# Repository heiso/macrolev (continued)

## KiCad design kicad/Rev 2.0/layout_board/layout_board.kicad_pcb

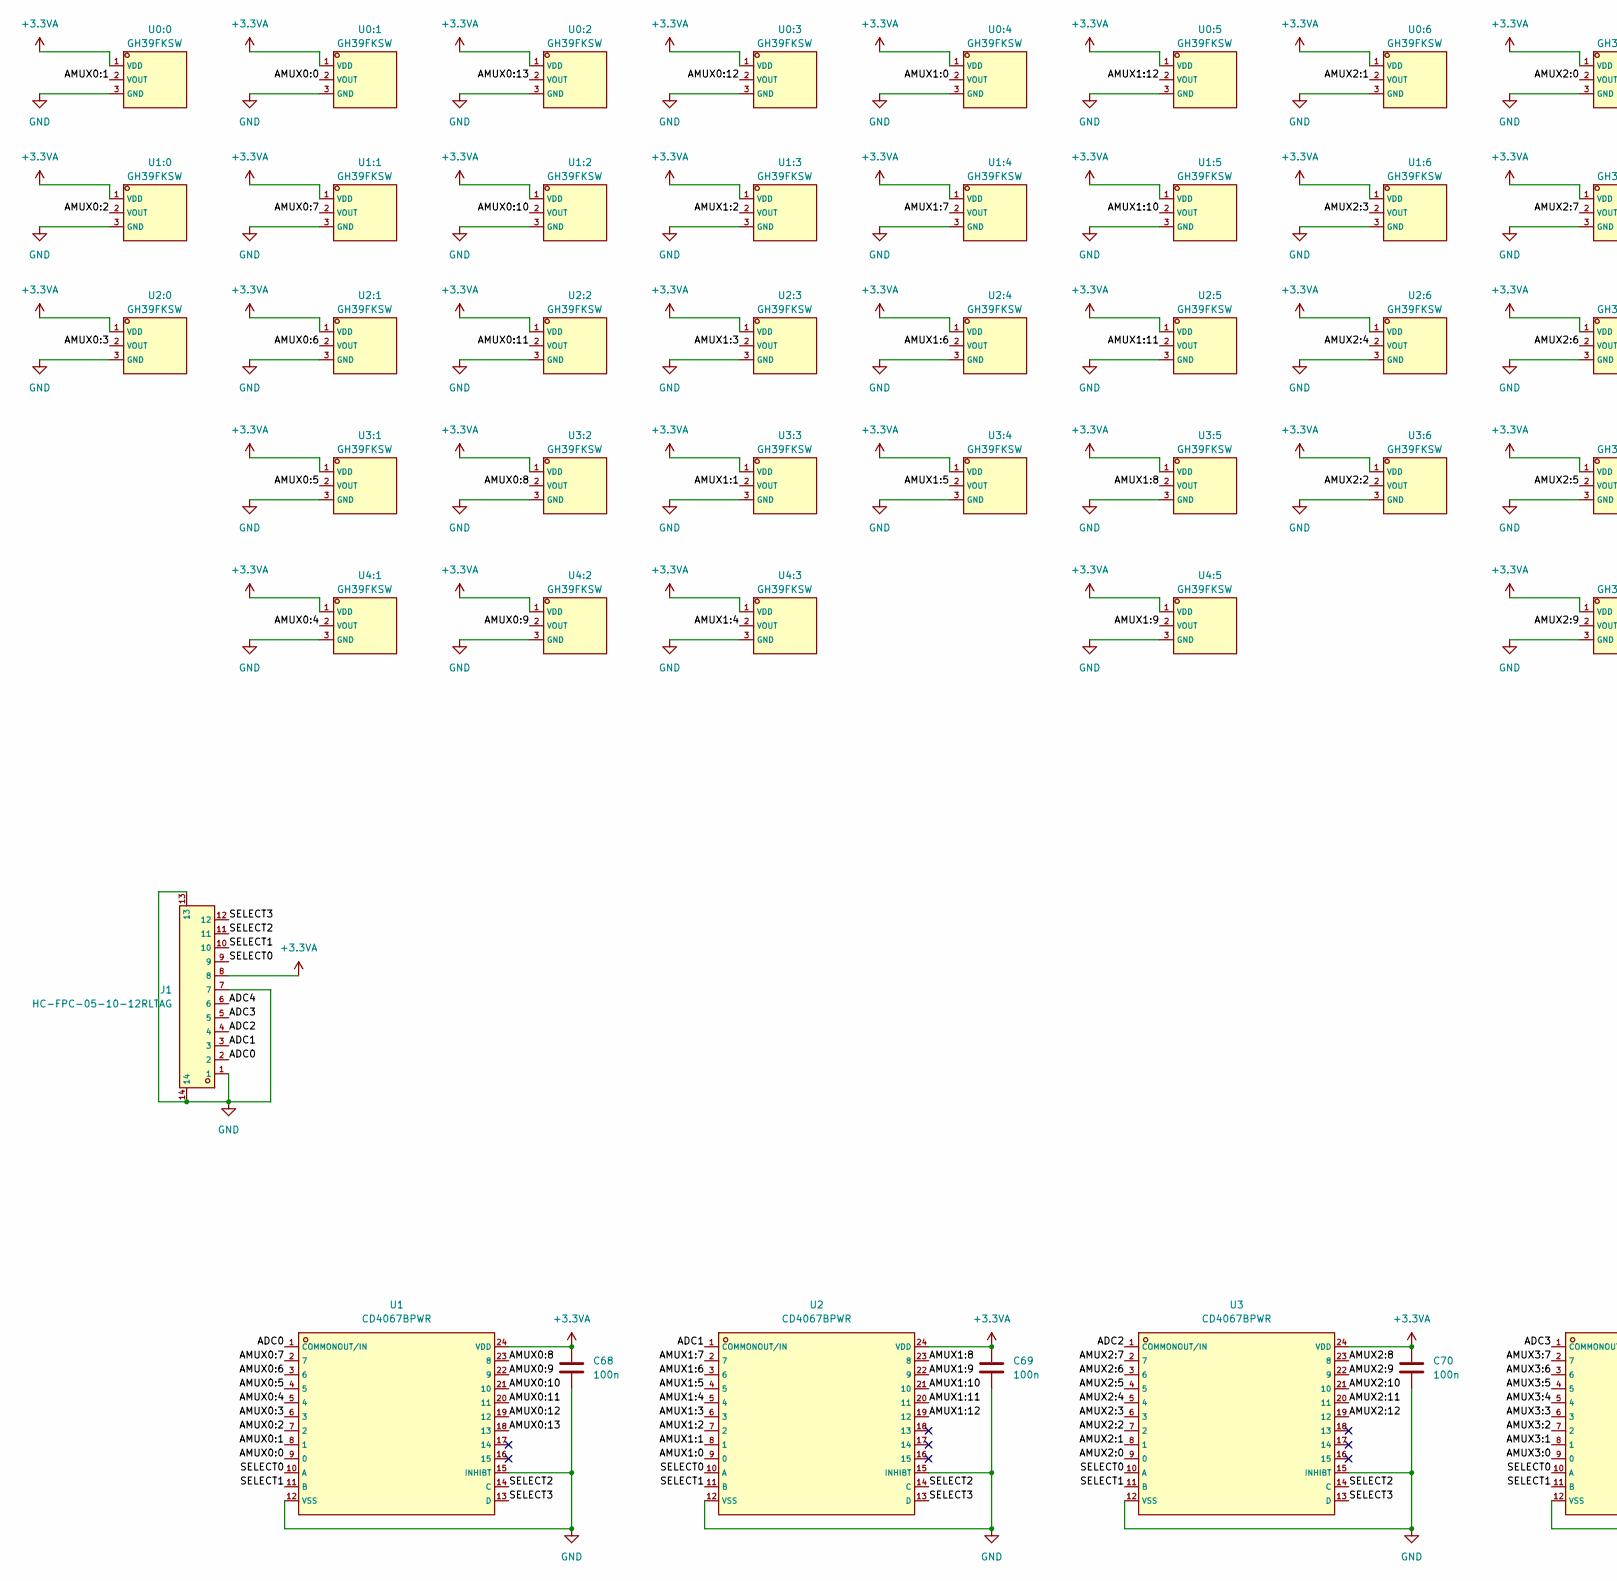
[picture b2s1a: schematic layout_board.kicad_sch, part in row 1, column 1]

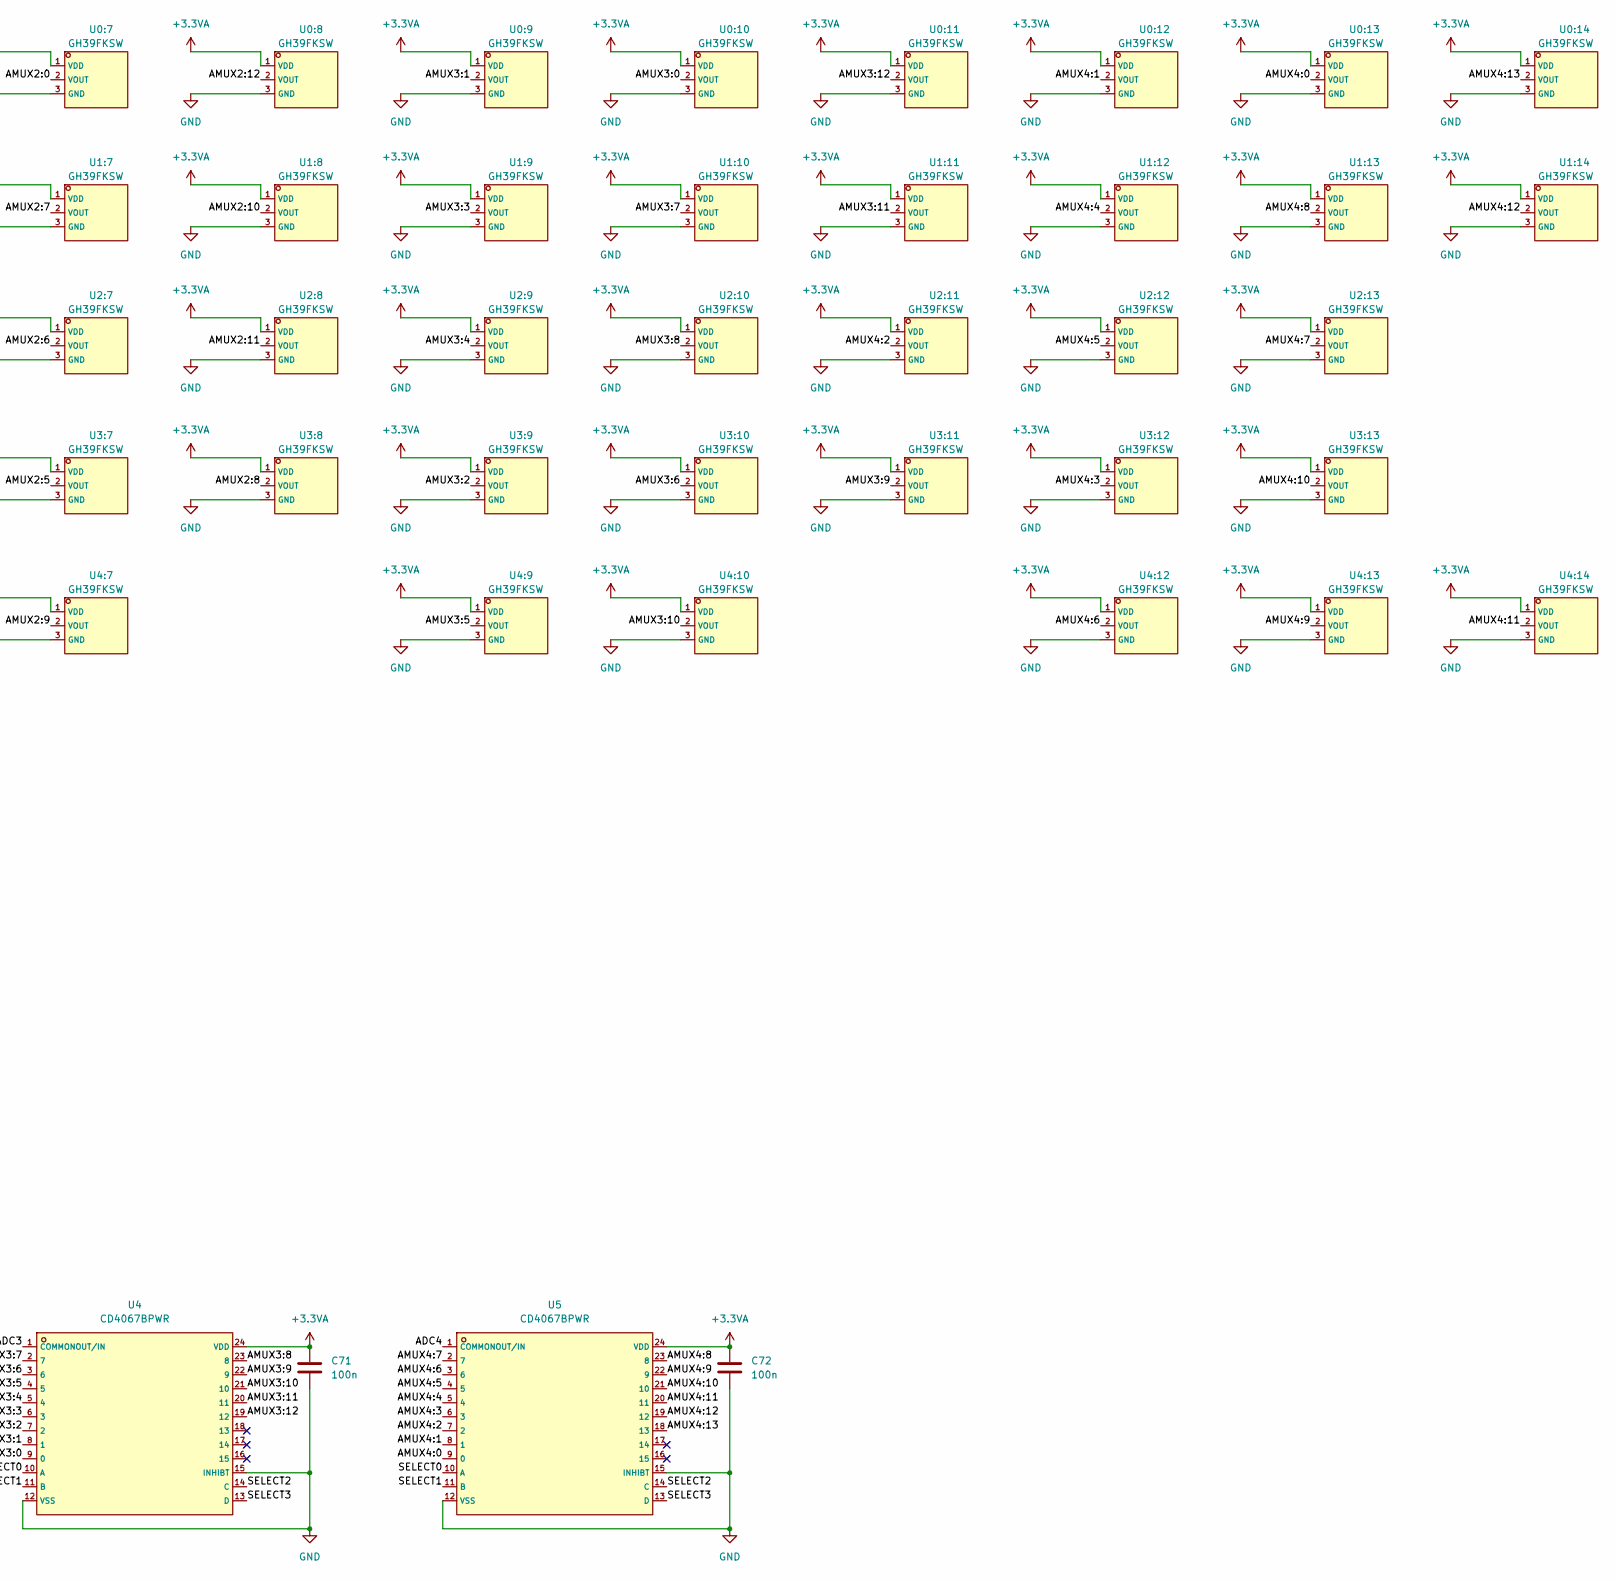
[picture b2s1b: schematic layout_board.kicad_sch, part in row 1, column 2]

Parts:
C68, C69, C70, C71, C72: 100n; C_0402_1005Metric_Pad0.74x0.62mm_HandSolder; LCSC C1525
J1: HC-FPC-05-10-12RLTAG; FPC-SMD_12P-P0.50_HCTL_HC-FPC-05-10-12RLTAG; LCSC C5213732
U0:0, U0:1, U0:2, U0:3, U0:4, U0:5, U0:6, U0:7, U0:8, U0:9, U0:10, U0:11, U0:12, U0:13, U0:14, U1:0, U1:1, U1:2, U1:3, U1:4, U1:5, U1:6, U1:7, U1:8, U1:9, U1:10, U1:11, U1:12, U1:13, U1:14, U2:0, U2:1, U2:2, U2:3, U2:4, U2:5, U2:6, U2:7, U2:8, U2:9, U2:10, U2:11, U2:12, U2:13, U3:1, U3:2, U3:3, U3:4, U3:5, U3:6, U3:7, U3:8, U3:9, U3:10, U3:11, U3:12, U3:13, U4:1, U4:2, U4:3, U4:5, U4:7, U4:9, U4:10, U4:12, U4:13, U4:14: GH39FKSW; SOT-23; LCSC C266230
U1, U2, U3, U4, U5: CD4067BPWR; SSOP-24_5.3x8.2mm_P0.65mm; LCSC C2861251

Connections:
+3.3VA: C68.1, C69.1, C70.1, C71.1, C72.1, J1.8, U0:0.1 (VDD), U0:1.1 (VDD), U0:2.1 (VDD), U0:3.1 (VDD), U0:4.1 (VDD), U0:5.1 (VDD), U0:6.1 (VDD), U0:7.1 (VDD), U0:8.1 (VDD), U0:9.1 (VDD), U0:10.1 (VDD), U0:11.1 (VDD), U0:12.1 (VDD), U0:13.1 (VDD), U0:14.1 (VDD), U1.24 (VDD), U1:0.1 (VDD), U1:1.1 (VDD), U1:2.1 (VDD), U1:3.1 (VDD), U1:4.1 (VDD), U1:5.1 (VDD), U1:6.1 (VDD), U1:7.1 (VDD), U1:8.1 (VDD), U1:9.1 (VDD), U1:10.1 (VDD), U1:11.1 (VDD), U1:12.1 (VDD), U1:13.1 (VDD), U1:14.1 (VDD), U2.24 (VDD), U2:0.1 (VDD), U2:1.1 (VDD), U2:2.1 (VDD), U2:3.1 (VDD), U2:4.1 (VDD), U2:5.1 (VDD), U2:6.1 (VDD), U2:7.1 (VDD), U2:8.1 (VDD), U2:9.1 (VDD), U2:10.1 (VDD), U2:11.1 (VDD), U2:12.1 (VDD), U2:13.1 (VDD), U3.24 (VDD), U3:1.1 (VDD), U3:2.1 (VDD), U3:3.1 (VDD), U3:4.1 (VDD), U3:5.1 (VDD), U3:6.1 (VDD), U3:7.1 (VDD), U3:8.1 (VDD), U3:9.1 (VDD), U3:10.1 (VDD), U3:11.1 (VDD), U3:12.1 (VDD), U3:13.1 (VDD), U4.24 (VDD), U4:1.1 (VDD), U4:2.1 (VDD), U4:3.1 (VDD), U4:5.1 (VDD), U4:7.1 (VDD), U4:9.1 (VDD), U4:10.1 (VDD), U4:12.1 (VDD), U4:13.1 (VDD), U4:14.1 (VDD), U5.24 (VDD)
/ADC0: J1.2, U1.1 (COMMONOUT/IN)
/ADC1: J1.3, U2.1 (COMMONOUT/IN)
/ADC2: J1.4, U3.1 (COMMONOUT/IN)
/ADC3: J1.5, U4.1 (COMMONOUT/IN)
/ADC4: J1.6, U5.1 (COMMONOUT/IN)
/AMUX0:0: U0:1.2 (VOUT), U1.9 (0)
/AMUX0:1: U0:0.2 (VOUT), U1.8 (1)
/AMUX0:2: U1.7 (2), U1:0.2 (VOUT)
/AMUX0:3: U1.6 (3), U2:0.2 (VOUT)
/AMUX0:4: U1.5 (4), U4:1.2 (VOUT)
/AMUX0:5: U1.4 (5), U3:1.2 (VOUT)
/AMUX0:6: U1.3 (6), U2:1.2 (VOUT)
/AMUX0:7: U1.2 (7), U1:1.2 (VOUT)
/AMUX0:8: U1.23 (8), U3:2.2 (VOUT)
/AMUX0:9: U1.22 (9), U4:2.2 (VOUT)
/AMUX0:10: U1.21 (10), U1:2.2 (VOUT)
/AMUX0:11: U1.20 (11), U2:2.2 (VOUT)
/AMUX0:12: U0:3.2 (VOUT), U1.19 (12)
/AMUX0:13: U0:2.2 (VOUT), U1.18 (13)
/AMUX1:0: U0:4.2 (VOUT), U2.9 (0)
/AMUX1:1: U2.8 (1), U3:3.2 (VOUT)
/AMUX1:2: U1:3.2 (VOUT), U2.7 (2)
/AMUX1:3: U2.6 (3), U2:3.2 (VOUT)
/AMUX1:4: U2.5 (4), U4:3.2 (VOUT)
/AMUX1:5: U2.4 (5), U3:4.2 (VOUT)
/AMUX1:6: U2.3 (6), U2:4.2 (VOUT)
/AMUX1:7: U1:4.2 (VOUT), U2.2 (7)
/AMUX1:8: U2.23 (8), U3:5.2 (VOUT)
/AMUX1:9: U2.22 (9), U4:5.2 (VOUT)
/AMUX1:10: U1:5.2 (VOUT), U2.21 (10)
/AMUX1:11: U2.20 (11), U2:5.2 (VOUT)
/AMUX1:12: U0:5.2 (VOUT), U2.19 (12)
/AMUX2:0: U0:7.2 (VOUT), U3.9 (0)
/AMUX2:1: U0:6.2 (VOUT), U3.8 (1)
/AMUX2:2: U3.7 (2), U3:6.2 (VOUT)
/AMUX2:3: U1:6.2 (VOUT), U3.6 (3)
/AMUX2:4: U2:6.2 (VOUT), U3.5 (4)
/AMUX2:5: U3.4 (5), U3:7.2 (VOUT)
/AMUX2:6: U2:7.2 (VOUT), U3.3 (6)
/AMUX2:7: U1:7.2 (VOUT), U3.2 (7)
/AMUX2:8: U3.23 (8), U3:8.2 (VOUT)
/AMUX2:9: U3.22 (9), U4:7.2 (VOUT)
/AMUX2:10: U1:8.2 (VOUT), U3.21 (10)
/AMUX2:11: U2:8.2 (VOUT), U3.20 (11)
/AMUX2:12: U0:8.2 (VOUT), U3.19 (12)
/AMUX3:0: U0:10.2 (VOUT), U4.9 (0)
/AMUX3:1: U0:9.2 (VOUT), U4.8 (1)
/AMUX3:2: U3:9.2 (VOUT), U4.7 (2)
/AMUX3:3: U1:9.2 (VOUT), U4.6 (3)
/AMUX3:4: U2:9.2 (VOUT), U4.5 (4)
/AMUX3:5: U4.4 (5), U4:9.2 (VOUT)
/AMUX3:6: U3:10.2 (VOUT), U4.3 (6)
/AMUX3:7: U1:10.2 (VOUT), U4.2 (7)
/AMUX3:8: U2:10.2 (VOUT), U4.23 (8)
/AMUX3:9: U3:11.2 (VOUT), U4.22 (9)
/AMUX3:10: U4.21 (10), U4:10.2 (VOUT)
/AMUX3:11: U1:11.2 (VOUT), U4.20 (11)
/AMUX3:12: U0:11.2 (VOUT), U4.19 (12)
/AMUX4:0: U0:13.2 (VOUT), U5.9 (0)
/AMUX4:1: U0:12.2 (VOUT), U5.8 (1)
/AMUX4:2: U2:11.2 (VOUT), U5.7 (2)
/AMUX4:3: U3:12.2 (VOUT), U5.6 (3)
/AMUX4:4: U1:12.2 (VOUT), U5.5 (4)
/AMUX4:5: U2:12.2 (VOUT), U5.4 (5)
/AMUX4:6: U4:12.2 (VOUT), U5.3 (6)
/AMUX4:7: U2:13.2 (VOUT), U5.2 (7)
/AMUX4:8: U1:13.2 (VOUT), U5.23 (8)
/AMUX4:9: U4:13.2 (VOUT), U5.22 (9)
/AMUX4:10: U3:13.2 (VOUT), U5.21 (10)
/AMUX4:11: U4:14.2 (VOUT), U5.20 (11)
/AMUX4:12: U1:14.2 (VOUT), U5.19 (12)
/AMUX4:13: U0:14.2 (VOUT), U5.18 (13)
/SELECT0: J1.9, U1.10 (A), U2.10 (A), U3.10 (A), U4.10 (A), U5.10 (A)
/SELECT1: J1.10, U1.11 (B), U2.11 (B), U3.11 (B), U4.11 (B), U5.11 (B)
/SELECT2: J1.11, U1.14 (C), U2.14 (C), U3.14 (C), U4.14 (C), U5.14 (C)
/SELECT3: J1.12, U1.13 (D), U2.13 (D), U3.13 (D), U4.13 (D), U5.13 (D)
GND: C68.2, C69.2, C70.2, C71.2, C72.2, J1.1, J1.7, J1.13, J1.14, U0:0.3 (GND), U0:1.3 (GND), U0:2.3 (GND), U0:3.3 (GND), U0:4.3 (GND), U0:5.3 (GND), U0:6.3 (GND), U0:7.3 (GND), U0:8.3 (GND), U0:9.3 (GND), U0:10.3 (GND), U0:11.3 (GND), U0:12.3 (GND), U0:13.3 (GND), U0:14.3 (GND), U1.12 (VSS), U1.15 (INHIBT), U1:0.3 (GND), U1:1.3 (GND), U1:2.3 (GND), U1:3.3 (GND), U1:4.3 (GND), U1:5.3 (GND), U1:6.3 (GND), U1:7.3 (GND), U1:8.3 (GND), U1:9.3 (GND), U1:10.3 (GND), U1:11.3 (GND), U1:12.3 (GND), U1:13.3 (GND), U1:14.3 (GND), U2.12 (VSS), U2.15 (INHIBT), U2:0.3 (GND), U2:1.3 (GND), U2:2.3 (GND), U2:3.3 (GND), U2:4.3 (GND), U2:5.3 (GND), U2:6.3 (GND), U2:7.3 (GND), U2:8.3 (GND), U2:9.3 (GND), U2:10.3 (GND), U2:11.3 (GND), U2:12.3 (GND), U2:13.3 (GND), U3.12 (VSS), U3.15 (INHIBT), U3:1.3 (GND), U3:2.3 (GND), U3:3.3 (GND), U3:4.3 (GND), U3:5.3 (GND), U3:6.3 (GND), U3:7.3 (GND), U3:8.3 (GND), U3:9.3 (GND), U3:10.3 (GND), U3:11.3 (GND), U3:12.3 (GND), U3:13.3 (GND), U4.12 (VSS), U4.15 (INHIBT), U4:1.3 (GND), U4:2.3 (GND), U4:3.3 (GND), U4:5.3 (GND), U4:7.3 (GND), U4:9.3 (GND), U4:10.3 (GND), U4:12.3 (GND), U4:13.3 (GND), U4:14.3 (GND), U5.12 (VSS), U5.15 (INHIBT)

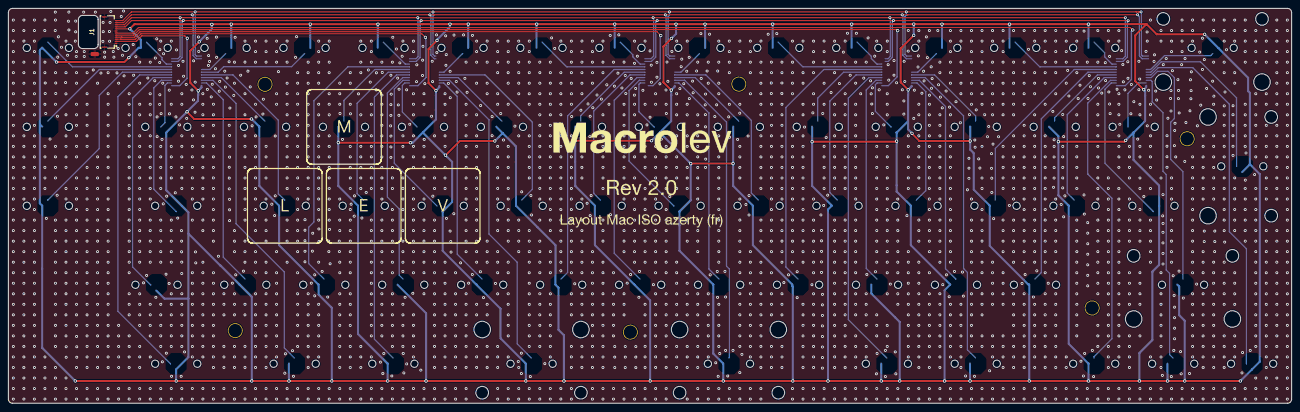
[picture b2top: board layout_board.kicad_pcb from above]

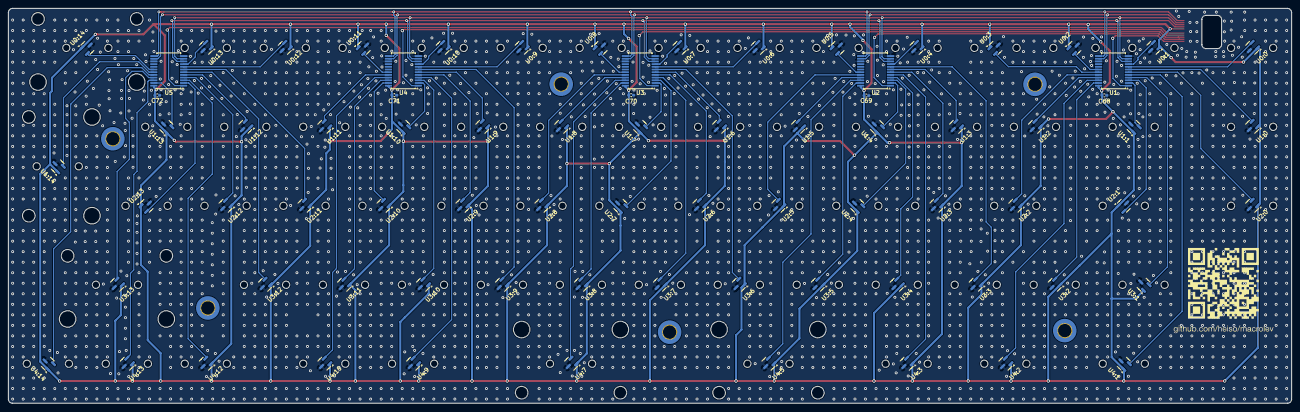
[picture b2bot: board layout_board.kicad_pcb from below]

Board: 2 copper layers, 309.6 x 95.2 mm, 78 parts (77 on the bottom side), 78 nets.

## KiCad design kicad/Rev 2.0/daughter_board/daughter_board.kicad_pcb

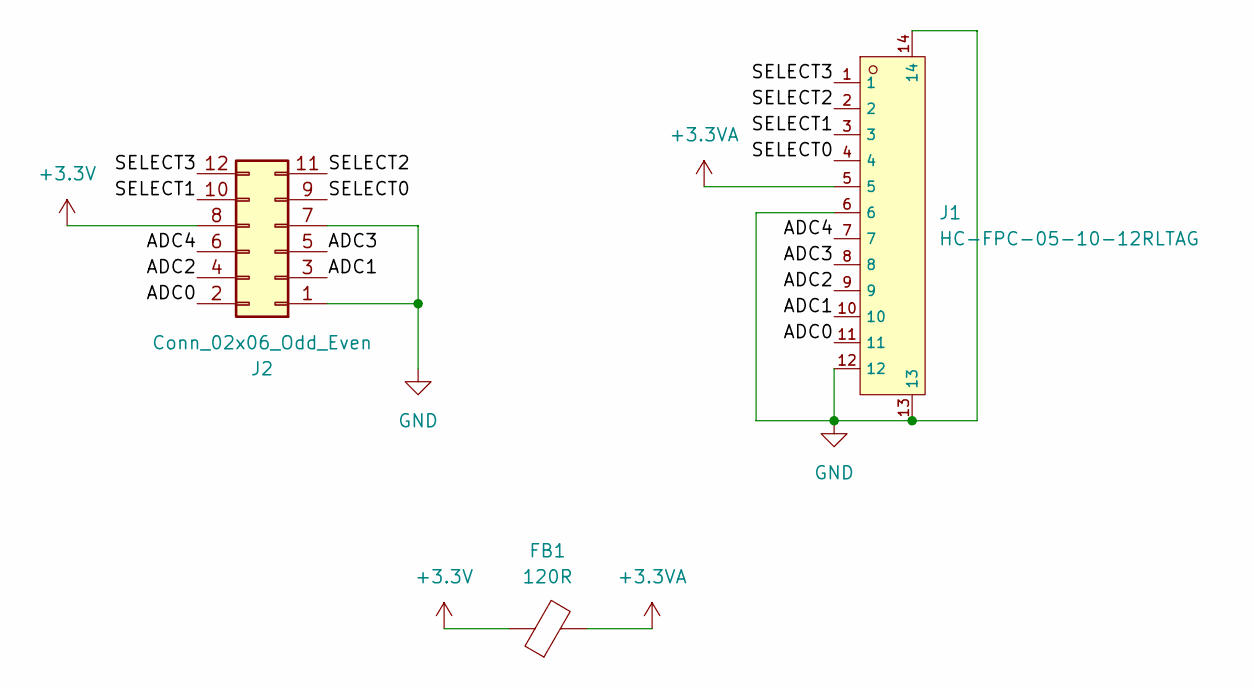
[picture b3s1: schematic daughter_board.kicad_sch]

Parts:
FB1: 120R; L_0603_1608Metric_Pad1.05x0.95mm_HandSolder; LCSC C76892
J1: HC-FPC-05-10-12RLTAG; FPC-SMD_12P-P0.50_HCTL_HC-FPC-05-10-12RLTAG; LCSC C5213732
J2: Conn_02x06_Odd_Even; PinHeader_2x06_P2.54mm_Horizontal

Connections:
+3.3V: FB1.1, J2.8
+3.3VA: FB1.2, J1.5
/ADC0: J1.11, J2.2
/ADC1: J1.10, J2.3
/ADC2: J1.9, J2.4
/ADC3: J1.8, J2.5
/ADC4: J1.7, J2.6
/SELECT0: J1.4, J2.9
/SELECT1: J1.3, J2.10
/SELECT2: J1.2, J2.11
/SELECT3: J1.1, J2.12
GND: J1.6, J1.12, J1.13, J1.14, J2.1, J2.7

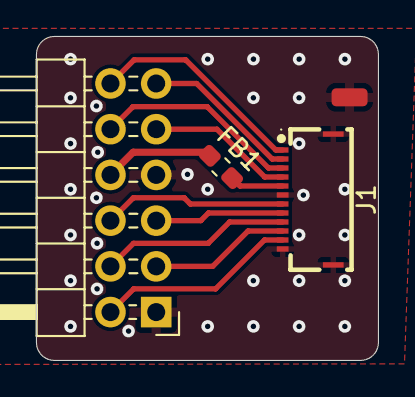
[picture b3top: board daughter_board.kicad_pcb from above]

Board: 2 copper layers, 19.0 x 18.0 mm, 3 parts (0 on the bottom side), 12 nets.

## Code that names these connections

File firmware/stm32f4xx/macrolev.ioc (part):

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Mcu.Name=STM32F411C(C-E)Ux
Mcu.Package=UFQFPN48
Mcu.UserName=STM32F411CEUx
PA11.Mode=Device_Only
PA11.Signal=USB_OTG_FS_DM
PA12.Mode=Device_Only
PA12.Signal=USB_OTG_FS_DP
PA13.Signal=SYS_JTMS-SWDIO
PA14.Signal=SYS_JTCK-SWCLK
PA3.Signal=ADCx_IN3
PA4.Signal=ADCx_IN4
PA5.Signal=ADCx_IN5
PA6.Signal=ADCx_IN6
PA7.Signal=ADCx_IN7
PB12.Signal=GPIO_Output
PB13.Signal=GPIO_Output
PB14.Signal=GPIO_Output
PB15.Signal=GPIO_Output
PB6.GPIOParameters=GPIO_Pu
PB6.GPIO_Pu=GPIO_PULLUP
PB6.Mode=I2C
PB6.Signal=I2C1_SCL
PB7.GPIOParameters=GPIO_Pu
PB7.GPIO_Pu=GPIO_PULLUP
PB7.Mode=I2C
PB7.Signal=I2C1_SDA
PH0\ -\ OSC_IN.Mode=HSE-External-Oscillator
PH0\ -\ OSC_IN.Signal=RCC_OSC_IN
PH1\ -\ OSC_OUT.Mode=HSE-External-Oscillator
PH1\ -\ OSC_OUT.Signal=RCC_OSC_OUT
RCC.HSE_VALUE=26000000
RCC.SYSCLKFreq_VALUE=26000000
RCC.SYSCLKSource=RCC_SYSCLKSOURCE_HSE
board=custom

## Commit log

2022-08-24 🎉 Abracadabra
2022-08-25 🚧 Push input still not working, keyb recognized
2022-09-06 🔥 Remove firmware from repository
2022-09-10 🚧 Chamfered knob design
2022-09-10 🚧 Playin with a design
2022-09-12 🚧 Trying NopSCADlib
2022-09-14 🚧 Stable outer shell
2022-09-14 🚧 Bulkier design
2022-09-16 🚧 First proto
2022-09-22 🚚 Move back firmware, remove nopscadlib
2022-09-25 ♻️ New macrolev design, proto void switch
2022-09-27 🚧 POC adc sample working
2022-09-27 ✨ Switches working
2022-09-27 ✨ Keymap is now in config
2022-09-30 ♻️ Improve hall effect data processing
2022-10-12 ✨ Now working with key modifiers
2022-10-14 ⚗️ Trying kicad, prototype "plastic pcb"
2022-11-07 🚧 Pcb in progress
2023-01-17 📝 Add wooting 60HE pictures
2023-09-28 heyboard-layout-editor to scad and new kicad project
2023-10-03 refactor readme file and remove old things
2023-10-26 pcb rev1.0
2023-10-27 doc(pcb): add pcb documentation
2023-10-31 fix(pcb): apply feedback from PrintedCircuitBoard sub
2023-11-06 change pcb routing
2023-11-08 add caps on amux, change routing
2023-11-10 update kle layout
2023-11-22 feat: first stm32 firmware implem and test
2023-11-23 poc working, commiting before swapping usb library to tinyUSB (stm32MX one is meh)
2023-11-27 rework and nearly working
2023-11-28 gtrying tinyusb
2023-11-30 firmware working with cubeide framework
2023-11-30 hey it's working
2023-11-30 opti
2023-11-30 clean
2023-12-01 add media keys
2023-12-03 improve tap mode
2023-12-03 add generic inout hid and debug mode
2023-12-03 Add graph to web app
2023-12-09 lots of thing isn't it ?
2023-12-11 improve webapp
2023-12-14 feat: can now change trigger offset trough web-app
2023-12-24 feat: rapid trigger is working and configurable with the wep-app
2023-12-24 fix: tap layer would never trigger
2024-01-19 feat: migrate remix to vite
2024-01-19 feat: move from ssr to spa
2024-02-18 fix: fix hid descriptor for windows
2024-03-04 wip: fix pcb
2024-03-15 chore: upgrade remix spa mode
2024-04-08 chore: change CTA wording
2024-04-15 feat: use webusb instead of custominout hid report
2024-04-15 fix: fix gh-pages behaviors
2024-05-12 webusb is working
2024-05-12 fix: fix windows detection
2024-06-16 wip rev 1.1
2024-09-12 wip: real time key logging
2024-10-20 wip: explore haptic feedback
2024-10-20 doc: update readme
2024-10-20 doc: add pictures
2024-11-06 feat: let the keyboard scream
2024-11-11 wip: trying to trigger DFU mode from application
2024-11-11 fix: disable screaming mode, it blocked consumer keys
2024-11-12 feat: can now configure the timeout of a tap key
2024-11-13 wip: split firmware code
2024-11-14 wip: split hid code
2024-11-14 refacto: split code
2024-11-14 chore: cubeIDE config
2024-11-18 wip: starting new pcb Rev 2.0
2024-11-20 wip: rev 2.0 pcb
2024-11-25 wip: working on flex cable
2024-11-25 wip: flex connector
2024-11-26 wip: add connector on layout board
2024-11-28 wip: remove flex pcb
2024-11-28 wip: add logo and qrcode
2024-11-30 wip: added logo
2024-12-01 wip: daughter board init
2024-12-01 wip: daughter board done
2024-12-01 wip: gerber files
2024-12-01 wip: changing amuxes
2024-12-03 feat: get last cycle duration from web-app
2024-12-03 release: Rev 2.0 sent to be manufactured
2024-12-03 feat: get cycle duration
2024-12-11 wip: esp32 firmware
2025-01-01 wip: new configurator
2025-01-01 fix: deploy
2025-01-01 fix: basename
2025-01-04 clean: remove unused files and folders
2025-01-07 feat: can now use switches with inverted poles
2025-01-11 wip: add tabs and layout size
2025-01-18 wip: playing with esp-idf
2025-02-17 doc: add disclaimer
2025-02-17 wip: new web-app
2025-02-17 fix: github action update
2025-02-18 wip: add some ui on config page
2025-04-04 fix npm deps
2025-05-02 chore: upgrade packages
2025-05-02 chore: fix github pages
2025-05-11 chore: some cleaning in ui classes
2025-05-11 chore: set submodules to specific versions
2025-05-12 chore: fix gitignore
2025-05-18 wip: set usb hid and cdc
2025-05-19 wip: split code
2025-05-30 wip: json is maybe not the best way to store data in an embedded thingy
2025-06-30 doc: add yuzu layout in readme
2026-01-10 update: prolly finished the todo i.e set- GPIOs at the same time using bitmap on register
